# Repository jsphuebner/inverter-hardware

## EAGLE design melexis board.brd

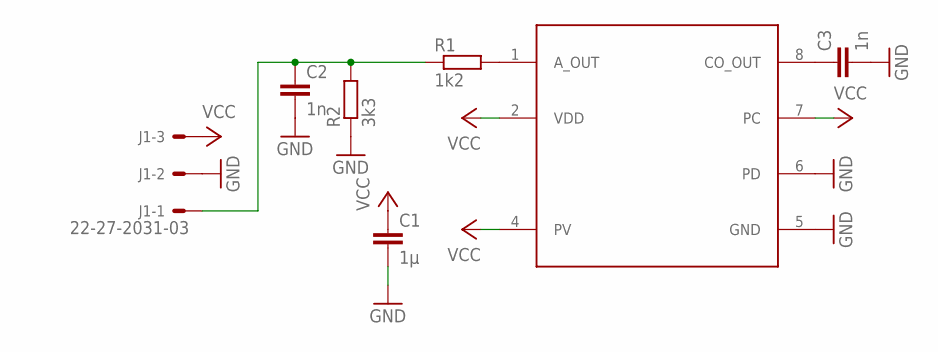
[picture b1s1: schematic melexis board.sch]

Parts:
C1: 1µ; C025-024X044
C2, C3: 1n; C025-024X044
IC1: MLX91205; SO-08
J1: 22-27-2031-03; 6410-03
R1: 1k2; 0204V
R2: 3k3; 0204V

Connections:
GND: C1.2, C2.2, C3.2, IC1.5 (GND), IC1.6 (PD), J1.2, R2.1
unnamed: IC1.1 (A_OUT), R1.2
unnamed: C3.1, IC1.8 (CO_OUT)
unnamed: C2.1, J1.1, R1.1, R2.2
VCC: C1.1, IC1.2 (VDD), IC1.4 (PV), IC1.7 (PC), J1.3

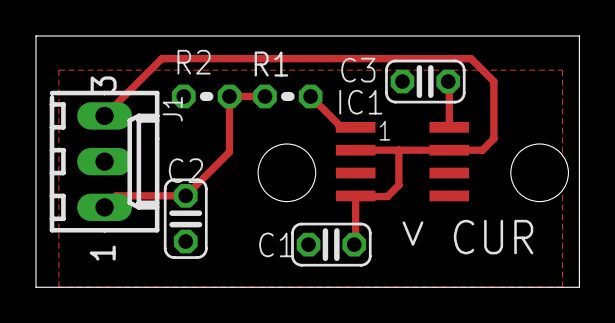
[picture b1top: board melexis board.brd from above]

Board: 2 copper layers, 30.2 x 14.0 mm, 7 parts (0 on the bottom side), 5 nets.
